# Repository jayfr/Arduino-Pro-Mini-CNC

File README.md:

Arduino-Pro-Mini-CNC
====================

CNC Millable version of the Arduino Pro Mini

For details, see http://www.robojay.us

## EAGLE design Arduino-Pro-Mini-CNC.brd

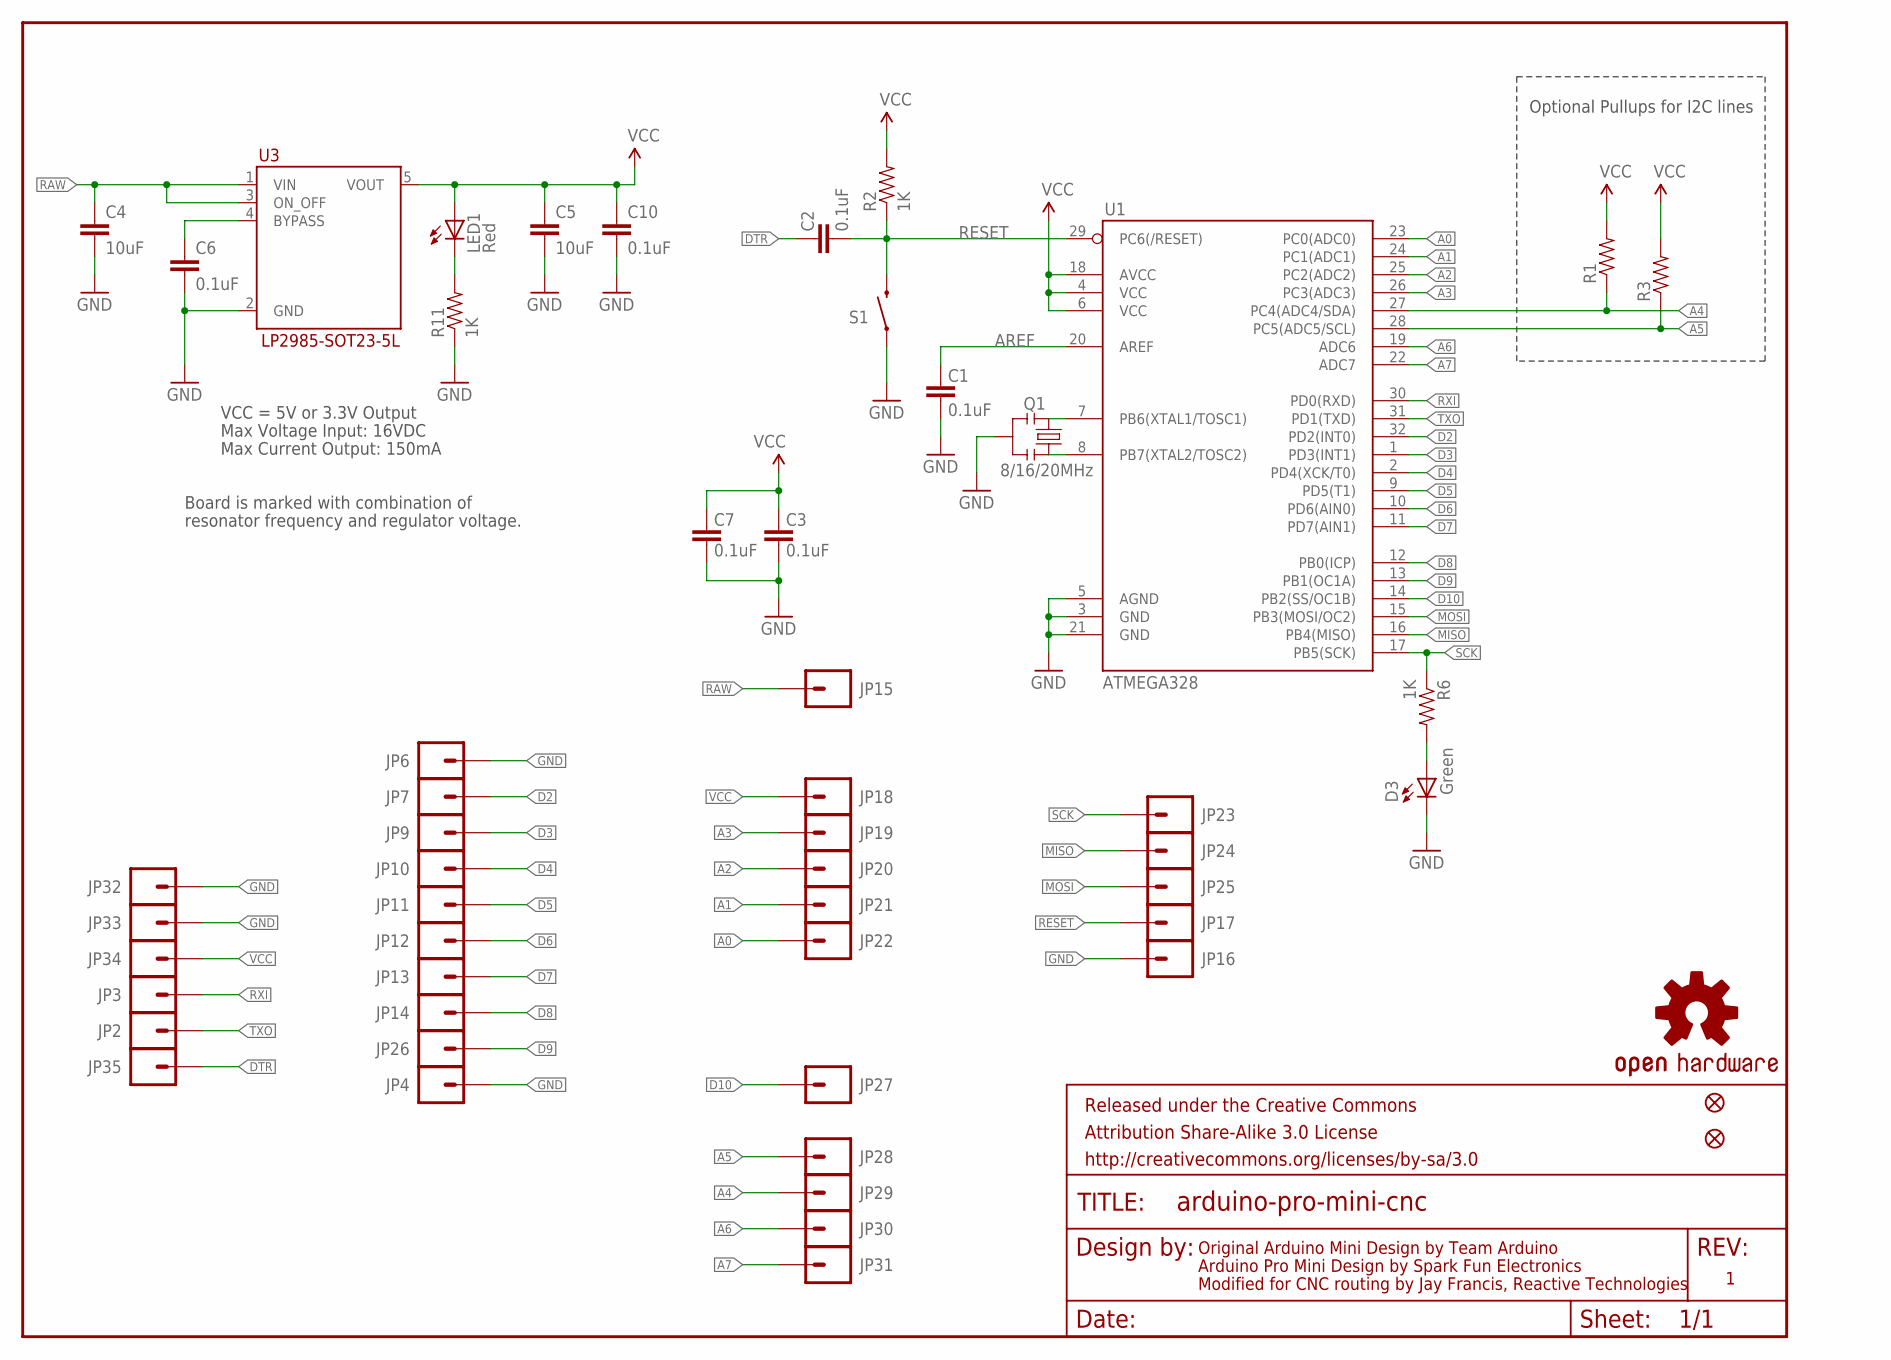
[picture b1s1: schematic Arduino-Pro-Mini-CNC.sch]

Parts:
C1, C2, C3, C6, C7, C10: 0.1uF; 0603-CAP
C4, C5: 10uF; 0603-CAP
D3: Green; 0603-LED-ALT1
FRAME1: FRAME-LETTER; CREATIVE_COMMONS
JP2, JP3, JP4, JP6, JP7, JP9, JP10, JP11, JP12, JP13, JP14, JP15, JP16, JP17, JP18, JP19, JP20, JP21, JP22, JP23, JP24, JP25, JP26, JP27, JP28, JP29, JP30, JP31, JP32, JP33, JP34, JP35: M01SMD_160X40; PAD-160-040
JP5, JP8: FIDUCIALUFIDUCIAL; MICRO-FIDUCIAL
LED1: Red; 0603-LED-ALT1
Q1: 8/16/20MHz; RESONATOR-SMD-1:1
R1, R3: RESISTOR0603-RES; 0603-RES
R2, R6, R11: 1K; 0603-RES
S1: SWITCH-MOMENTARY-2-OMRON-B3U-1000P; TACTILE-SWITCH-OMRON-B3U-1000P
U1: ATMEGA328; TQFP32-08
U3: LP2985-SOT23-5L; SOT23-5L
U$3: OSHW-LOGOS; OSHW-LOGO-S

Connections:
A0: JP22.P$1, U1.23 (PC0(ADC0))
A1: JP21.P$1, U1.24 (PC1(ADC1))
A2: JP20.P$1, U1.25 (PC2(ADC2))
A3: JP19.P$1, U1.26 (PC3(ADC3))
A4: JP29.P$1, R1.1, U1.27 (PC4(ADC4/SDA))
A5: JP28.P$1, R3.1, U1.28 (PC5(ADC5/SCL))
A6: JP30.P$1, U1.19 (ADC6)
A7: JP31.P$1, U1.22 (ADC7)
AREF: C1.2, U1.20 (AREF)
D2: JP7.P$1, U1.32 (PD2(INT0))
D3: JP9.P$1, U1.1 (PD3(INT1))
D4: JP10.P$1, U1.2 (PD4(XCK/T0))
D5: JP11.P$1, U1.9 (PD5(T1))
D6: JP12.P$1, U1.10 (PD6(AIN0))
D7: JP13.P$1, U1.11 (PD7(AIN1))
D8: JP14.P$1, U1.12 (PB0(ICP))
D9: JP26.P$1, U1.13 (PB1(OC1A))
D10: JP27.P$1, U1.14 (PB2(SS/OC1B))
DTR: C2.2, JP35.P$1
GND: C1.1, C3.1, C4.2, C5.2, C6.2, C7.1, C10.2, D3.C, JP4.P$1, JP6.P$1, JP16.P$1, JP32.P$1, JP33.P$1, Q1.2, R11.1, S1.P$1 (1), U1.3 (GND), U1.5 (AGND), U1.21 (GND), U3.2 (GND)
MISO: JP24.P$1, U1.16 (PB4(MISO))
MOSI: JP25.P$1, U1.15 (PB3(MOSI/OC2))
unnamed: Q1.3, U1.8 (PB7(XTAL2/TOSC2))
unnamed: Q1.1, U1.7 (PB6(XTAL1/TOSC1))
unnamed: LED1.C, R11.2
unnamed: C6.1, U3.4 (BYPASS)
unnamed: D3.A, R6.2
RAW: C4.1, JP15.P$1, U3.1 (VIN), U3.3 (ON_OFF)
RESET: C2.1, JP17.P$1, R2.1, S1.P$2 (2), U1.29 (PC6(/RESET))
RXI: JP3.P$1, U1.30 (PD0(RXD))
SCK: JP23.P$1, R6.1, U1.17 (PB5(SCK))
TXO: JP2.P$1, U1.31 (PD1(TXD))
VCC: C3.2, C5.1, C7.2, C10.1, JP18.P$1, JP34.P$1, LED1.A, R1.2, R2.2, R3.2, U1.4 (VCC), U1.6 (VCC), U1.18 (AVCC), U3.5 (VOUT)

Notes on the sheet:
Original Arduino Mini Design by Team Arduino
Arduino Pro Mini Design by Spark Fun Electronics
Max Voltage Input: 16VDC
Max Current Output: 150mA
Board is marked with combination of
resonator frequency and regulator voltage.
VCC = 5V or 3.3V Output
Optional Pullups for I2C lines
Modified for CNC routing by Jay Francis, Reactive Technologies

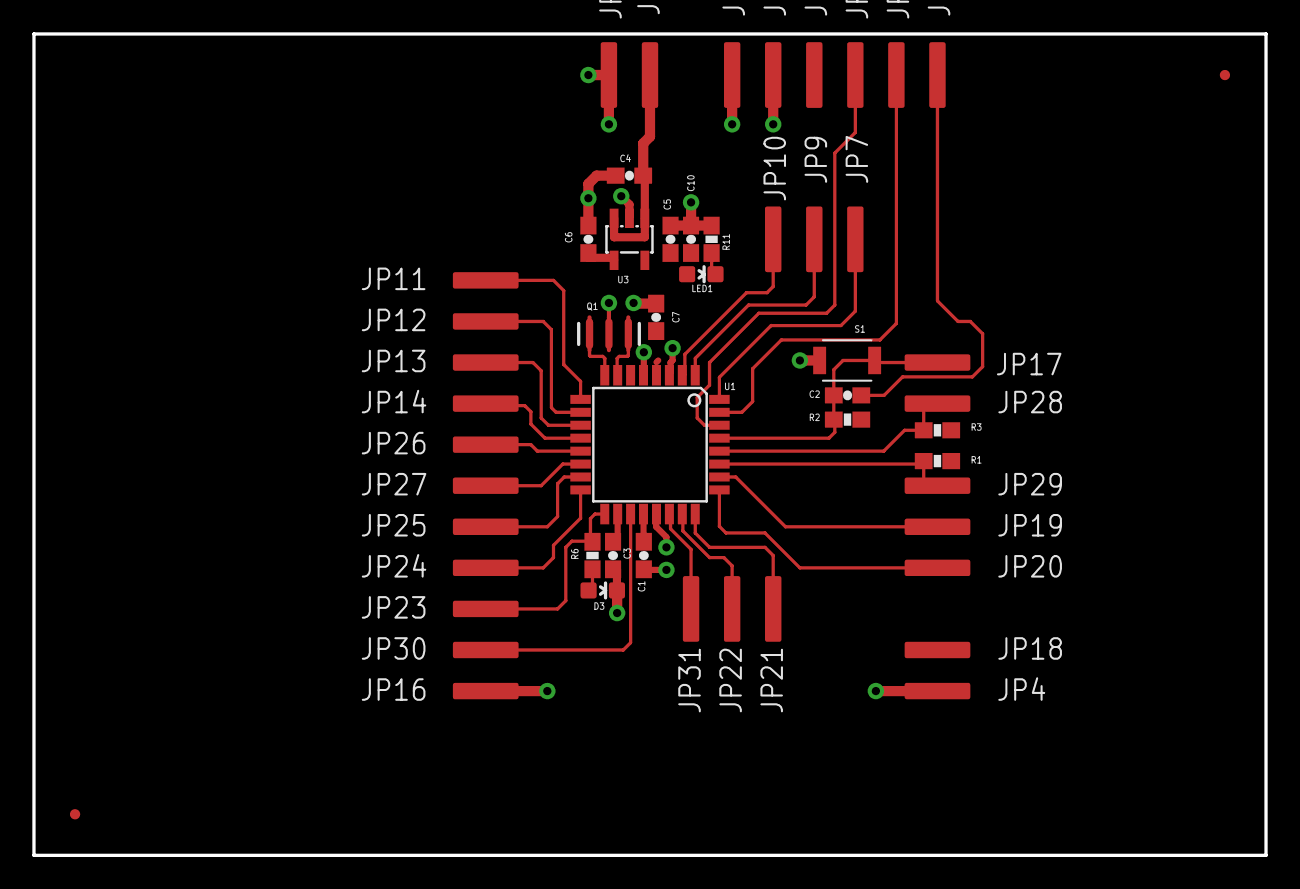
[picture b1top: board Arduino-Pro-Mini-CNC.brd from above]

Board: 2 copper layers, 76.2 x 50.8 mm, 55 parts (0 on the bottom side), 33 nets.

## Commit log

2014-08-17 Initial Commit
    Creation

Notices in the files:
parts and their libraries:
SparkFun-Aesthetics: Licensing: CC v3.0 Share-Alike You are welcome to use this library for commercial purposes.
SparkFun-Aesthetics: Released under the Creative Commons Attribution Share-Alike 3.0 License
SparkFun-Aesthetics: http://creativecommons.org/licenses/by-sa/3.0
